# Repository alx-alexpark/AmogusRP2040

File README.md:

# AmogusRP2040
An RP2040 devboard in the shape of an Among US Crewmate. It also includes a piezoelectric buzzer to play a melody and a button

https://github.com/user-attachments/assets/4d1c6cb2-48c5-49af-99a7-d3afa99e834c

## Images (Automatically rendered)

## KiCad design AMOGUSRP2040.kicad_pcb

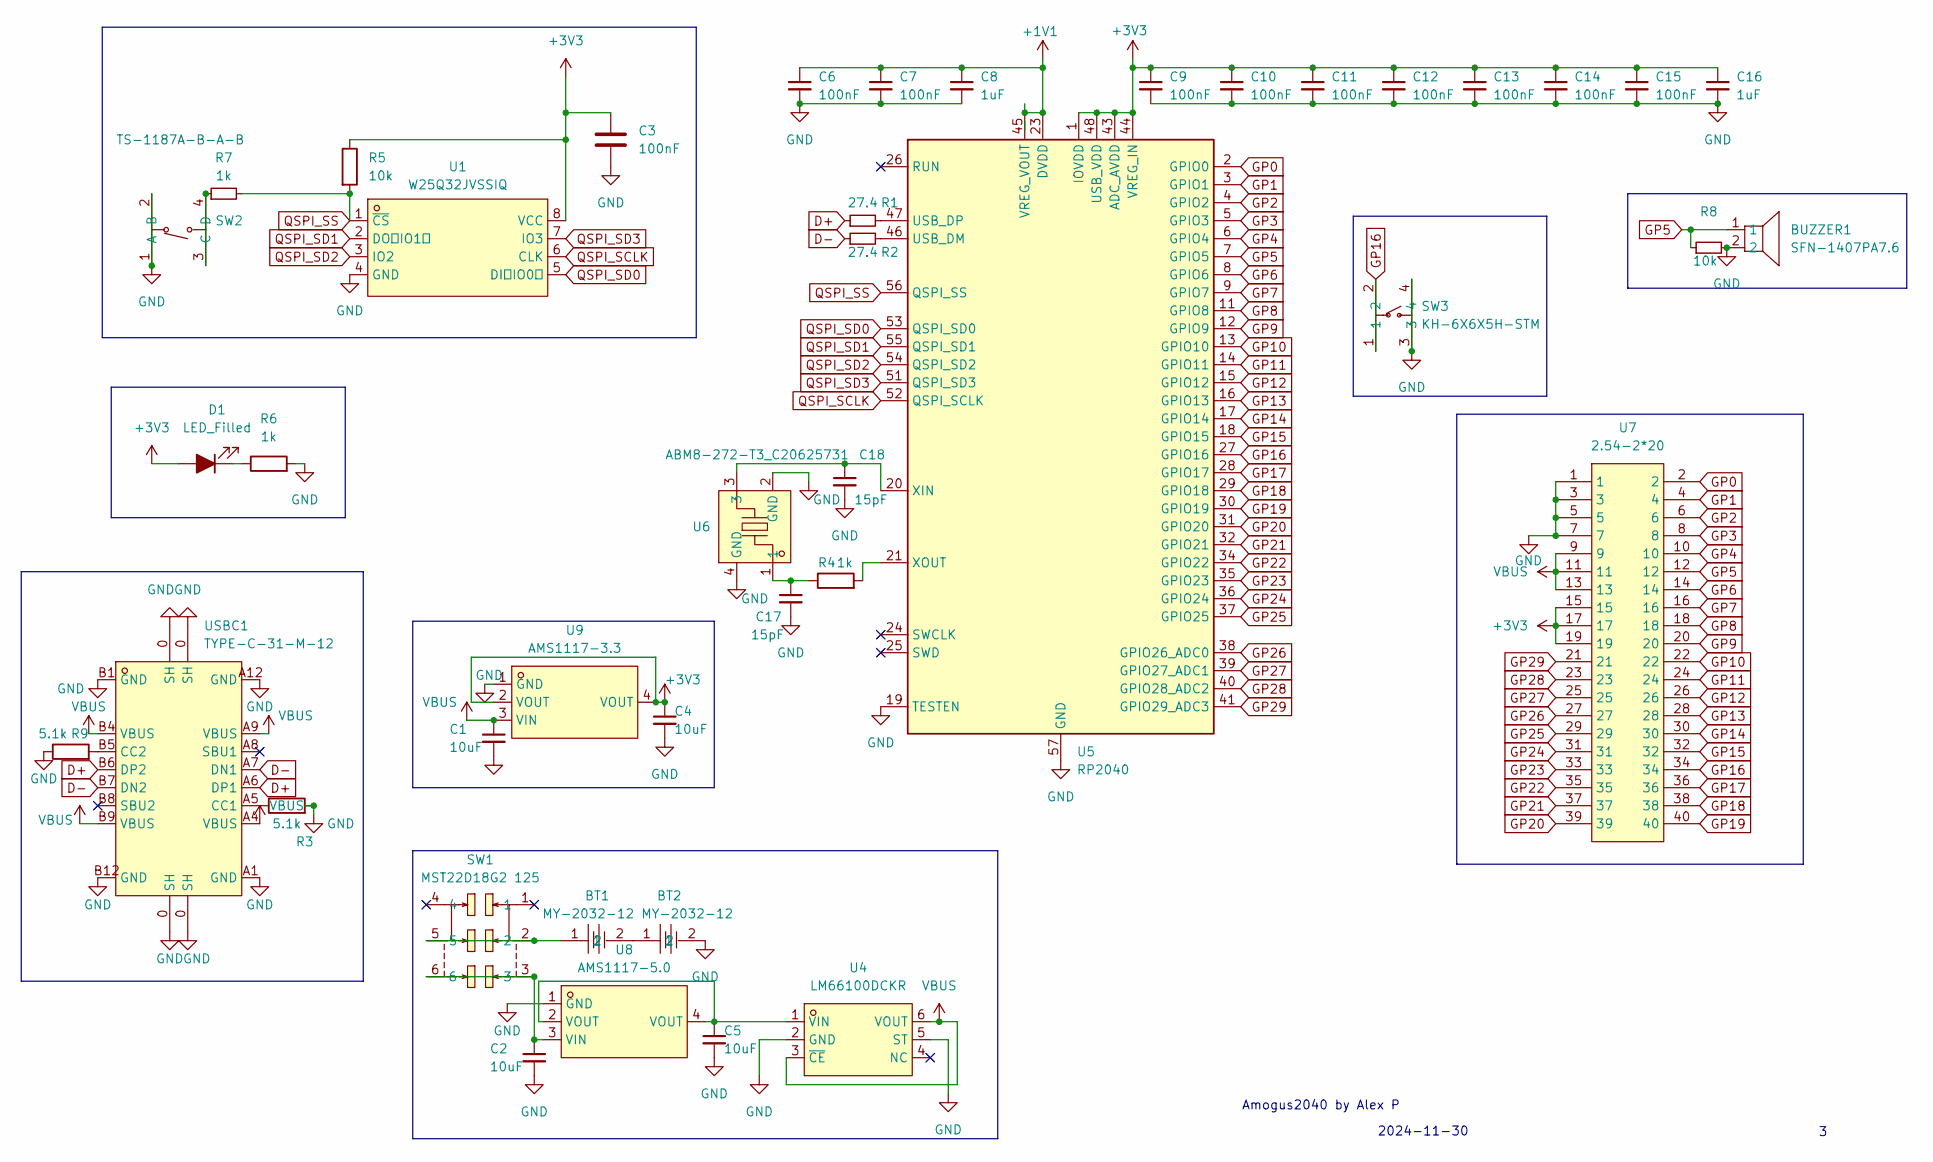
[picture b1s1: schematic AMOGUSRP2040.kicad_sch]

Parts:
BT1, BT2: MY-2032-12; BAT-SMD_MY-2032-12; LCSC Part C964833
BUZZER1: SFN-1407PA7.6; BUZ-TH_BD14.0-P7.60-D0.7; LCSC Part C360603
C1, C2, C4, C5: 10uF; C_1206_3216Metric; LCSC Part C7171
C3, C6, C7, C9, C10, C11, C12, C13, C14, C15: 100nF; C_0402_1005Metric; LCSC Part C1525
C8, C16: 1uF; C_0402_1005Metric; LCSC Part C52923
C17, C18: 15pF; C_0402_1005Metric; LCSC Part C1548
D1: LED_Filled; LED_0603_1608Metric; LCSC Part C2286
R1, R2: 27.4; R_0603_1608Metric; LCSC Part C5126244
R3, R9: 5.1k; R_0603_1608Metric; LCSC Part C23186
R4, R6, R7: 1k; R_0402_1005Metric; LCSC Part C11702
R5, R8: 10k; R_0805_2012Metric; LCSC Part C17414
SW1: MST22D18G2 125; SW-SMD_MST22D18G2; LCSC Part C2906280
SW2: TS-1187A-B-A-B; SW-SMD_4P-L5.1-W5.1-P3.70-LS6.5-TL_H1.5; LCSC Part C318884
SW3: KH-6X6X5H-STM; SW-SMD_4P-L6.0-W6.0-P4.50-LS9.0-2; LCSC Part C2837531
U1: W25Q32JVSSIQ; SOIC-8_L5.3-W5.3-P1.27-LS8.0-BL; LCSC Part C82344
U4: LM66100DCKR; SC-70-6_L2.0-W1.3-P0.65-LS2.1-BL; LCSC Part C2869734
U5: RP2040; QFN-56-1EP_7x7mm_P0.4mm_EP3.2x3.2mm; LCSC Part C2040
U6: ABM8-272-T3_C20625731; CRYSTAL-SMD_4P-L3.2-W2.5-BL; LCSC Part C20625731
U7: 2.54-2*20; HDR-TH_40P-P2.54-V-F-R2-C20-S2.54; LCSC Part C2977589
U8: AMS1117-5.0; SOT-223_L6.5-W3.5-P2.30-LS7.0-BR; LCSC Part C6187
U9: AMS1117-3.3; SOT-223-3_L6.5-W3.4-P2.30-LS7.0-BR; LCSC Part C6186
USBC1: TYPE-C-31-M-12; USB-C_SMD-TYPE-C-31-M-12; LCSC Part C165948

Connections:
+1V1: C6.1, C7.1, C8.1, U5.23 (DVDD), U5.45 (VREG_VOUT), U5.50 (DVDD)
+3V3: C3.1, C4.1, C9.1, C10.1, C11.1, C12.1, C13.1, C14.1, C15.1, C16.1, D1.2 (A), R5.1, U1.8 (VCC), U5.1 (IOVDD), U5.10 (IOVDD), U5.22 (IOVDD), U5.33 (IOVDD), U5.42 (IOVDD), U5.43 (ADC_AVDD), U5.44 (VREG_IN), U5.48 (USB_VDD), U5.49 (IOVDD), U7.15, U7.17, U7.19, U9.2 (VOUT), U9.4 (VOUT)
D+: R1.1, USBC1.A6 (DP1), USBC1.B6 (DP2)
D-: R2.1, USBC1.A7 (DN1), USBC1.B7 (DN2)
GND: BT2.2, BUZZER1.2, C1.2, C2.2, C3.2, C4.2, C5.2, C6.2, C7.2, C8.2, C9.2, C10.2, C11.2, C12.2, C13.2, C14.2, C15.2, C16.2, C17.2, C18.2, R3.2, R6.2, R8.2, R9.1, SW2.1 (A), SW2.2 (B), SW3.3, SW3.4, U1.4 (GND), U4.2 (GND), U4.5 (ST), U5.19 (TESTEN), U5.57 (GND), U6.2 (GND), U6.4 (GND), U7.1, U7.3, U7.5, U7.7, U8.1 (GND), U9.1 (GND), USBC1.0 (SH), USBC1.A1 (GND), USBC1.A12 (GND), USBC1.B1 (GND), USBC1.B12 (GND)
GP0: U5.2 (GPIO0), U7.2
GP1: U5.3 (GPIO1), U7.4
GP2: U5.4 (GPIO2), U7.6
GP3: U5.5 (GPIO3), U7.8
GP4: U5.6 (GPIO4), U7.10
GP5: BUZZER1.1, R8.1, U5.7 (GPIO5), U7.12
GP6: U5.8 (GPIO6), U7.14
GP7: U5.9 (GPIO7), U7.16
GP8: U5.11 (GPIO8), U7.18
GP9: U5.12 (GPIO9), U7.20
GP10: U5.13 (GPIO10), U7.22
GP11: U5.14 (GPIO11), U7.24
GP12: U5.15 (GPIO12), U7.26
GP13: U5.16 (GPIO13), U7.28
GP14: U5.17 (GPIO14), U7.30
GP15: U5.18 (GPIO15), U7.32
GP16: SW3.1, SW3.2, U5.27 (GPIO16), U7.34
GP17: U5.28 (GPIO17), U7.36
GP18: U5.29 (GPIO18), U7.38
GP19: U5.30 (GPIO19), U7.40
GP20: U5.31 (GPIO20), U7.39
GP21: U5.32 (GPIO21), U7.37
GP22: U5.34 (GPIO22), U7.35
GP23: U5.35 (GPIO23), U7.33
GP24: U5.36 (GPIO24), U7.31
GP25: U5.37 (GPIO25), U7.29
GP26: U5.38 (GPIO26_ADC0), U7.27
GP27: U5.39 (GPIO27_ADC1), U7.25
GP28: U5.40 (GPIO28_ADC2), U7.23
GP29: U5.41 (GPIO29_ADC3), U7.21
unnamed: BT1.1, SW1.2, SW1.5
unnamed: BT1.2, BT2.1
unnamed: C17.1, R4.1, U6.1
unnamed: D1.1 (K), R6.1
unnamed: R7.1, SW2.3 (C), SW2.4 (D)
unnamed: C5.1, U4.1 (VIN), U8.2 (VOUT), U8.4 (VOUT)
unnamed: R2.2, U5.46 (USB_DM)
unnamed: R1.2, U5.47 (USB_DP)
unnamed: C18.1, U5.20 (XIN), U6.3
unnamed: R4.2, U5.21 (XOUT)
unnamed: C2.1, SW1.3, SW1.6, U8.3 (VIN)
unnamed: R3.1, USBC1.A5 (CC1)
unnamed: R9.2, USBC1.B5 (CC2)
QSPI_SCLK: U1.6 (CLK), U5.52 (QSPI_SCLK)
QSPI_SD0: U1.5 (DI（IO0）), U5.53 (QSPI_SD0)
QSPI_SD1: U1.2 (DO（IO1）), U5.55 (QSPI_SD1)
QSPI_SD2: U1.3 (IO2), U5.54 (QSPI_SD2)
QSPI_SD3: U1.7 (IO3), U5.51 (QSPI_SD3)
QSPI_SS: R5.2, R7.2, U1.1 (~CS), U5.56 (QSPI_SS)
VBUS: C1.1, U4.3 (~CE), U4.6 (VOUT), U7.9, U7.11, U7.13, U9.3 (VIN), USBC1.A4 (VBUS), USBC1.A9 (VBUS), USBC1.B4 (VBUS), USBC1.B9 (VBUS)

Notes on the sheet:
Amogus2040 by Alex P
2024-11-30

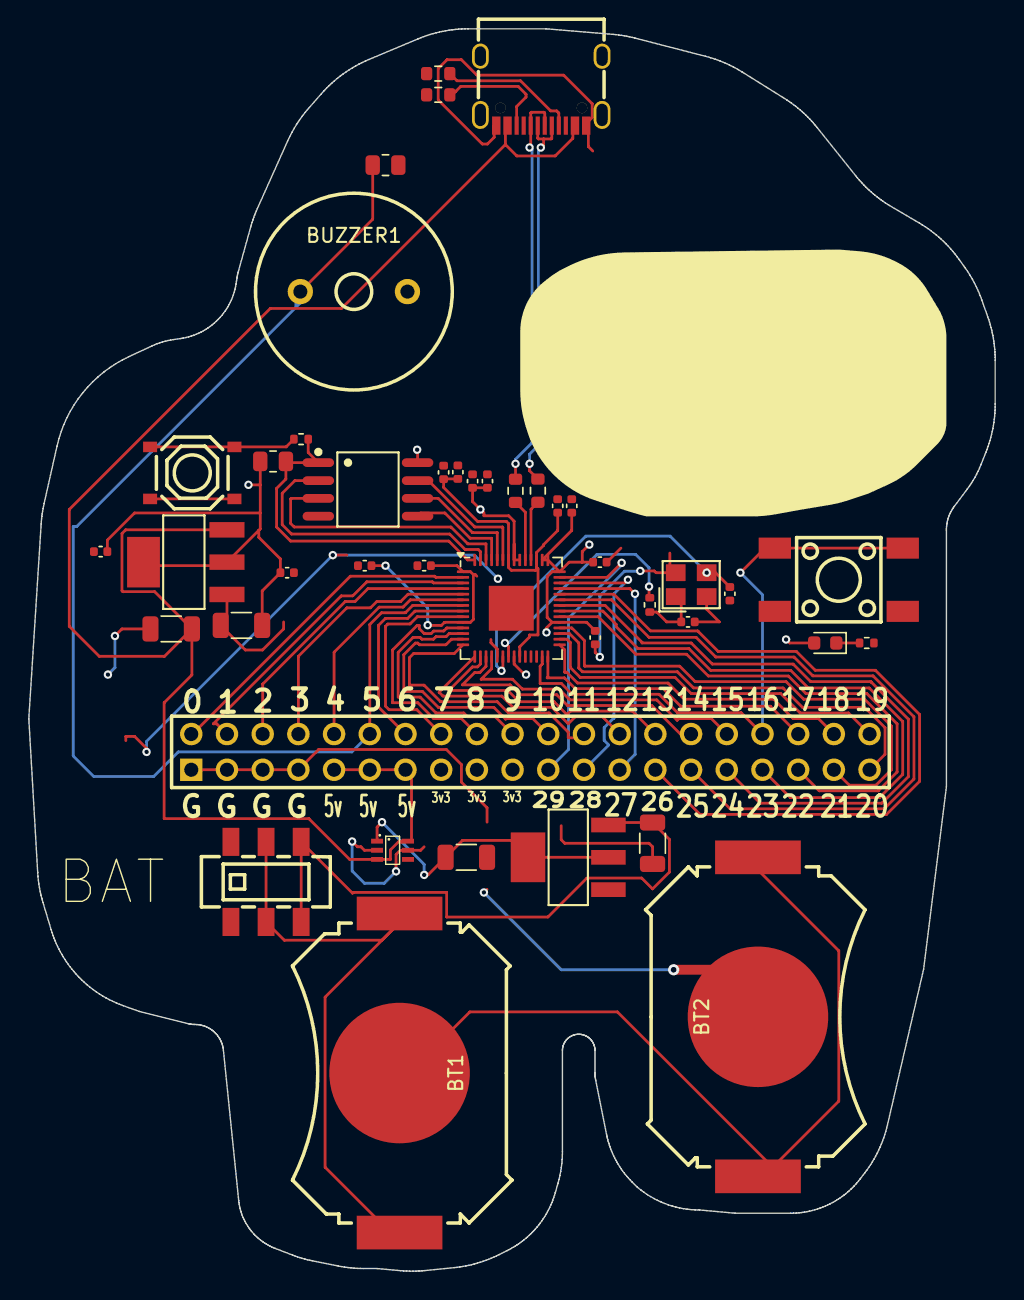
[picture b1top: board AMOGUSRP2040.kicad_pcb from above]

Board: 2 copper layers, 68.8 x 88.4 mm, 42 parts (0 on the bottom side), 55 nets.

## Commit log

2024-12-06 Apply gitignore
2024-12-06 remove jlcpcb/
2024-12-22 add video
2025-02-10 pcb images
2025-02-10 add gif
